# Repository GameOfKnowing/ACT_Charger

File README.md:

# ACT_Charger
A modular, Arduino-based charger for charging and measuring the capacities of many small lithium-polymer batteries

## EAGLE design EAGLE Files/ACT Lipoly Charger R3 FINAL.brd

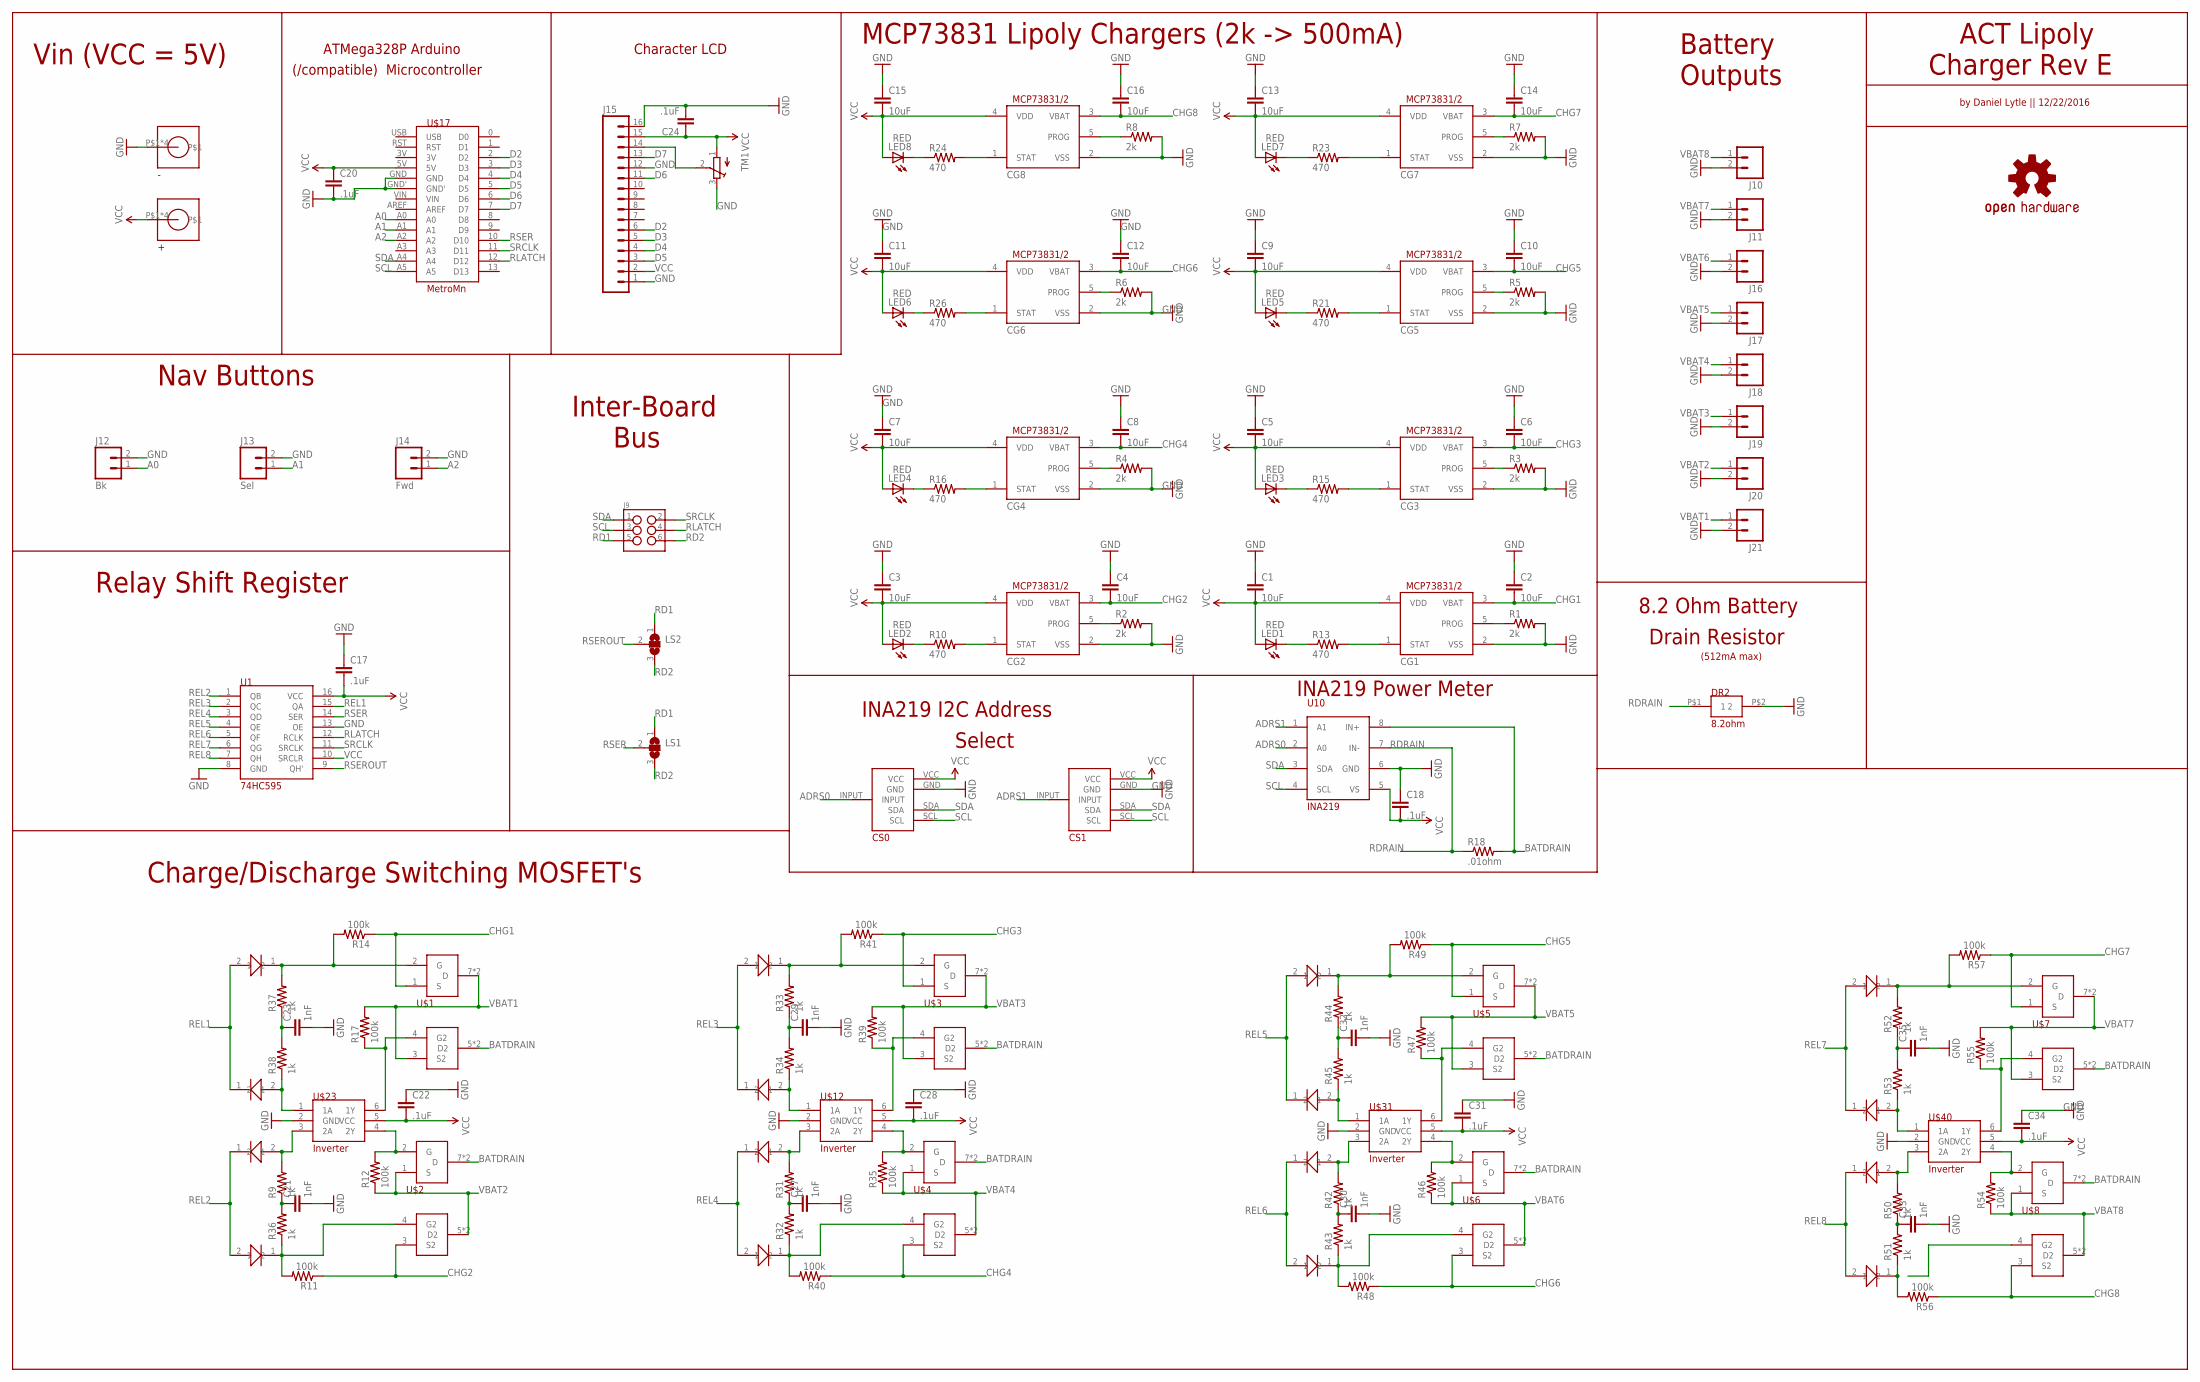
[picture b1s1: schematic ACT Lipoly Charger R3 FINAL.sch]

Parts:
+: 8191-SEMS; 9191-SEMS
-: 8191-SEMS; 9191-SEMS
C1, C2, C3, C4, C5, C6, C7, C8, C9, C10, C11, C12, C13, C14, C15, C16: 10uF; 0805
C17, C18, C20, C22, C24, C28, C31, C34: .1uF; 0805
C21, C23, C27, C29, C30, C32, C33, C35: 1nF; 0805
CG1, CG2, CG3, CG4, CG5, CG6, CG7, CG8: MCP73831/OT; SOT23-5L
CS0, CS1: 4-WAYSELECTOR
DR2: 8.2ohm; UB5C-5R6F1
J9: M03X2FEMALE; 2X3
J10, J11, J16, J17, J18, J19, J20, J21: M02LOCK_LONGPADS; 1X02_LOCK_LONGPADS
J12: Bk; 1X02_LOCK_LONGPADS
J13: Sel; 1X02_LOCK_LONGPADS
J14: Fwd; 1X02_LOCK_LONGPADS
J15: M16LOCK_LONGPADS; 1X16_LOCK_LONGPADS
LED1, LED2, LED3, LED4, LED5, LED6, LED7, LED8: RED; CHIP-LED0805
LS1, LS2: SJ2W; SJ_2
R1, R2, R3, R4, R5, R6, R7, R8: 2k; 0805
R9, R31, R32, R33, R34, R36, R37, R38, R42, R43, R44, R45, R50, R51, R52, R53: 1k; 0805
R10, R13, R15, R16, R21, R23, R24, R26: 470; 0805
R11, R12, R14, R17, R35, R39, R40, R41, R46, R47, R48, R49, R54, R55, R56, R57: 100k; 0805
R18: .01ohm; 0805
TM1: TRIMPOTTC33X; TC33X
U1: 74HC595; DIL16
U10: INA219; SOIC8
U$1, U$2, U$3, U$4, U$5, U$6, U$7, U$8: DMP3085LSD; SOIC8
U$12, U$23, U$31, U$40: Inverter; SOT363_PHILIPS
U$15, U$16, U$18, U$19, U$26, U$27, U$28, U$29, U$34, U$35, U$36, U$37, U$43, U$44, U$45, U$46: DA2J10100L_DIODE; SOD323
U$17: MetroMn; ADAFRUIT_METRO_MINI
VCC: OSHW-LOGOM-COPPER; OSHW-LOGO-M_COPPER

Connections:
A0: J12.1, U$17.A0
A1: J13.1, U$17.A1
A2: J14.1, U$17.A2
ADRS0: CS0.INPUT, U10.2 (A0)
ADRS1: CS1.INPUT, U10.1 (A1)
BATDRAIN: R18.2, U10.8 (IN+), U$1.5 (D2), U$1.6 (D2), U$2.7 (D), U$2.8 (D), U$3.5 (D2), U$3.6 (D2), U$4.7 (D), U$4.8 (D), U$5.5 (D2), U$5.6 (D2), U$6.7 (D), U$6.8 (D), U$7.5 (D2), U$7.6 (D2), U$8.7 (D), U$8.8 (D)
CHG1: C2.2, CG1.3 (VBAT), R14.1, U$1.1 (S)
CHG2: C4.2, CG2.3 (VBAT), R11.1, U$2.3 (S2)
CHG3: C6.2, CG3.3 (VBAT), R41.1, U$3.1 (S)
CHG4: C8.2, CG4.3 (VBAT), R40.1, U$4.3 (S2)
CHG5: C10.2, CG5.3 (VBAT), R49.1, U$5.1 (S)
CHG6: C12.2, CG6.3 (VBAT), R48.1, U$6.3 (S2)
CHG7: C14.2, CG7.3 (VBAT), R57.1, U$7.1 (S)
CHG8: C16.2, CG8.3 (VBAT), R56.1, U$8.3 (S2)
D2: J15.6, U$17.2 (D2)
D3: J15.5, U$17.3 (D3)
D4: J15.4, U$17.4 (D4)
D5: J15.3, U$17.5 (D5)
D6: J15.11, U$17.6 (D6)
D7: J15.13, U$17.7 (D7)
GND: -.P$1, -.P$2, -.P$3, -.P$4, C1.1, C2.1, C3.1, C4.1, C5.1, C6.1, C7.1, C8.1, C9.1, C10.1, C11.1, C12.1, C13.1, C14.1, C15.1, C16.1, C17.1, C18.1, C20.2, C21.2, C22.1, C23.2, C24.2, C27.2, C28.1, C29.2, C30.2, C31.1, C32.2, C33.2, C34.1, C35.2, CG1.2 (VSS), CG2.2 (VSS), CG3.2 (VSS), CG4.2 (VSS), CG5.2 (VSS), CG6.2 (VSS), CG7.2 (VSS), CG8.2 (VSS), CS0.GND, CS1.GND, DR2.P$2 (2), J10.2, J11.2, J12.2, J13.2, J14.2, J15.1, J15.12, J15.16, J16.2, J17.2, J18.2, J19.2, J20.2, J21.2, R1.2, R2.2, R3.2, R4.2, R5.2, R6.2, R7.2, R8.2, TM1.3 (E), U1.8 (GND), U1.13 (OE), U10.6 (GND), U$12.2 (GND), U$17.GND, U$17.GND', U$23.2 (GND), U$31.2 (GND), U$40.2 (GND)
unnamed: CG7.1 (STAT), R23.2
unnamed: CG8.5 (PROG), R8.1
unnamed: LED7.C, R23.1
unnamed: CG7.5 (PROG), R7.1
unnamed: CG6.5 (PROG), R6.1
unnamed: CG8.1 (STAT), R24.2
unnamed: CG5.5 (PROG), R5.1
unnamed: CG4.5 (PROG), R4.1
unnamed: LED8.C, R24.1
unnamed: CG3.5 (PROG), R3.1
unnamed: CG2.5 (PROG), R2.1
unnamed: LED6.C, R26.1
unnamed: CG1.5 (PROG), R1.1
unnamed: CG6.1 (STAT), R26.2
unnamed: CG4.1 (STAT), R16.2
unnamed: LED4.C, R16.1
unnamed: LED5.C, R21.1
unnamed: CG5.1 (STAT), R21.2
unnamed: LED3.C, R15.1
unnamed: CG3.1 (STAT), R15.2
unnamed: LED1.C, R13.1
unnamed: CG1.1 (STAT), R13.2
unnamed: CG2.1 (STAT), R10.2
unnamed: LED2.C, R10.1
unnamed: J15.14, TM1.2 (S)
unnamed: R38.1, U$23.1 (1A), U$29.2
unnamed: R9.2, U$23.3 (2A), U$28.2
unnamed: C21.1, R9.1, R36.2
unnamed: R11.2, R36.1, U$2.4 (G2), U$26.1
unnamed: R12.2, U$2.2 (G), U$23.4 (2Y)
unnamed: R17.1, U$1.4 (G2), U$23.6 (1Y)
unnamed: C23.1, R37.1, R38.2
unnamed: R14.2, R37.2, U$1.2 (G), U$27.1
unnamed: R31.2, U$12.3 (2A), U$16.2
unnamed: C27.1, R31.1, R32.2
unnamed: R32.1, R40.2, U$4.4 (G2), U$15.1
unnamed: R35.2, U$4.2 (G), U$12.4 (2Y)
unnamed: R34.1, U$12.1 (1A), U$19.2
unnamed: R39.1, U$3.4 (G2), U$12.6 (1Y)
unnamed: R33.2, R41.2, U$3.2 (G), U$18.1
unnamed: C29.1, R33.1, R34.2
unnamed: R42.2, U$31.3 (2A), U$35.2
unnamed: C30.1, R42.1, R43.2
unnamed: R43.1, R48.2, U$6.4 (G2), U$34.1
unnamed: R46.2, U$6.2 (G), U$31.4 (2Y)
unnamed: R45.1, U$31.1 (1A), U$37.2
unnamed: R47.1, U$5.4 (G2), U$31.6 (1Y)
unnamed: R44.2, R49.2, U$5.2 (G), U$36.1
unnamed: C32.1, R44.1, R45.2
unnamed: R50.2, U$40.3 (2A), U$44.2
unnamed: C33.1, R50.1, R51.2
unnamed: R51.1, R56.2, U$43.1
unnamed: R54.2, U$8.2 (G), U$40.4 (2Y)
unnamed: R53.1, U$40.1 (1A), U$46.2
unnamed: R55.1, U$7.4 (G2), U$40.6 (1Y)
unnamed: R52.2, R57.2, U$7.2 (G), U$45.1
unnamed: C35.1, R52.1, R53.2
RD1: J9.5, LS1.1, LS2.1
RD2: J9.6, LS1.3, LS2.3
RDRAIN: DR2.P$1 (1), R18.1, U10.7 (IN-)
REL1: U1.15 (QA), U$27.2, U$29.1
REL2: U1.1 (QB), U$26.2, U$28.1
REL3: U1.2 (QC), U$18.2, U$19.1
REL4: U1.3 (QD), U$15.2, U$16.1
REL5: U1.4 (QE), U$36.2, U$37.1
REL6: U1.5 (QF), U$34.2, U$35.1
REL7: U1.6 (QG), U$45.2, U$46.1
REL8: U1.7 (QH), U$43.2, U$44.1
RLATCH: J9.4, U1.12 (RCLK), U$17.12 (D12)
RSER: LS1.2, U1.14 (SER), U$17.10 (D10)
RSEROUT: LS2.2, U1.9 (QH')
SCL: CS0.SCL, CS1.SCL, J9.3, U10.4 (SCL), U$17.A5
SDA: CS0.SDA, CS1.SDA, J9.1, U10.3 (SDA), U$17.A4
SRCLK: J9.2, U1.11 (SRCLK), U$17.11 (D11)
VBAT1: J21.1, R17.2, U$1.3 (S2), U$1.7 (D), U$1.8 (D)
VBAT2: J20.1, R12.1, U$2.1 (S), U$2.5 (D2), U$2.6 (D2)
VBAT3: J19.1, R39.2, U$3.3 (S2), U$3.7 (D), U$3.8 (D)
VBAT4: J18.1, R35.1, U$4.1 (S), U$4.5 (D2), U$4.6 (D2)
VBAT5: J17.1, R47.2, U$5.3 (S2), U$5.7 (D), U$5.8 (D)
VBAT6: J16.1, R46.1, U$6.1 (S), U$6.5 (D2), U$6.6 (D2)
VBAT7: J11.1, R55.2, U$7.3 (S2), U$7.7 (D), U$7.8 (D)
VBAT8: J10.1, R54.1, U$8.1 (S), U$8.5 (D2), U$8.6 (D2)
VCC: +.P$1, +.P$2, +.P$3, +.P$4, C1.2, C3.2, C5.2, C7.2, C9.2, C11.2, C13.2, C15.2, C17.2, C18.2, C20.1, C22.2, C24.1, C28.2, C31.2, C34.2, CG1.4 (VDD), CG2.4 (VDD), CG3.4 (VDD), CG4.4 (VDD), CG5.4 (VDD), CG6.4 (VDD), CG7.4 (VDD), CG8.4 (VDD), CS0.VCC, CS1.VCC, J15.2, J15.15, LED1.A, LED2.A, LED3.A, LED4.A, LED5.A, LED6.A, LED7.A, LED8.A, TM1.1 (A), U1.10 (SRCLR), U1.16 (VCC), U10.5 (VS), U$12.5 (VCC), U$17.5V, U$23.5 (VCC), U$31.5 (VCC), U$40.5 (VCC)

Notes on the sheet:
ATMega328P Arduino
(/compatible) Microcontroller
Vin (VCC = 5V)
Character LCD
MCP73831 Lipoly Chargers (2k -> 500mA)
Relay Shift Register
Inter-Board
Bus
INA219 I2C Address
Select
INA219 Power Meter
8.2 Ohm Battery
Drain Resistor
Battery
Charge/Discharge Switching MOSFET's
ACT Lipoly
Charger Rev E
by Daniel Lytle || 12/22/2016
Outputs
Nav Buttons
(512mA max)

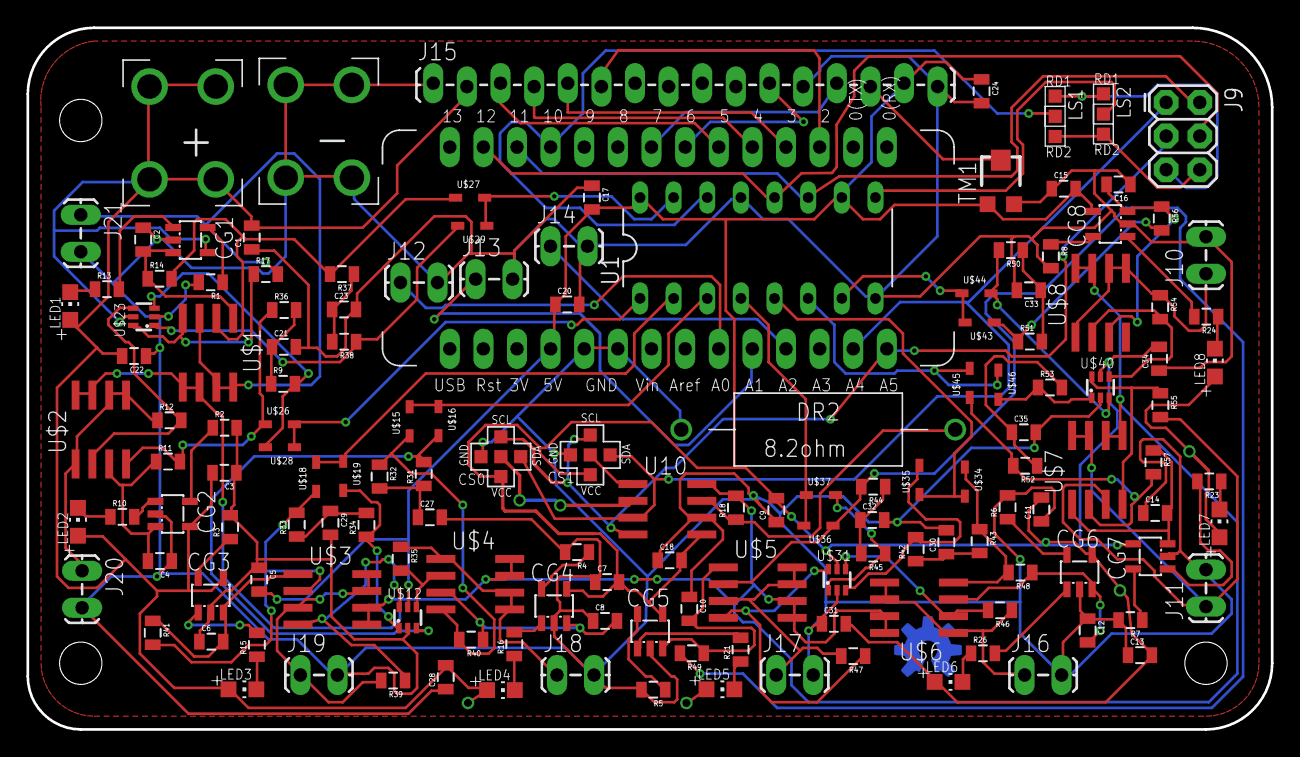
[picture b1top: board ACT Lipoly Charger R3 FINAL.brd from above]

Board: 2 copper layers, 94.0 x 53.0 mm, 150 parts (1 on the bottom side), 104 nets.

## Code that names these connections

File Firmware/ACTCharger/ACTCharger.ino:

//ACT Charger Firmware V. 1.3 
//Manages battery charging, discharging, and UI device functions
//This project's hardware and software are open-source under an MIT License
//GitHub: github.com/codebylytle/ACT_Charger
//by Daniel Lytle
//for the ACT (Automated Coordination of Teams) Lab at USC
//Lab Website: usc-actlab.github.io
//6.13.17
//

#include <Arduino.h>
#include <LiquidCrystal.h>
#include <Wire.h>
#include <Adafruit_INA219.h>

//initializes INA219 modues and their i2c addresses
Adafruit_INA219 ina219_A(0x40);
Adafruit_INA219 ina219_B(0x41);
Adafruit_INA219 ina219_C(0x42);
Adafruit_INA219 ina219_D(0x43);
Adafruit_INA219 ina219_E(0x44);
Adafruit_INA219 ina219_F(0x45);
Adafruit_INA219 ina219_G(0x46);
Adafruit_INA219 ina219_H(0x47);

//sets number of boards in current setup and the number of charging modules per board
const byte numBoards = 2;
const byte chargersperBoard = 8;
//sets minimum voltage (mV) that cells can reach during discharge
const float minV = 3.6;
//sets variable names for shift register pins
const byte RSER = 10;
const byte SRCLK = 11;
const byte RLATCH = 12;
//Names pushbutton pins
const int sel = A1;
const int fw = A2;
const int bk = A0;
//creates an array of bytes, each of which creates a different charge/discharge arrangement when
//shifted into the shift registers
byte registerBytes[9] = {0x00, 0x01, 0x02, 0x04, 0x08, 0x0F, 0x20, 0x40, 0x80};
//a friendlier decimal record of which module on each board is discharging
unsigned short discharging[numBoards];
//tracks the capacity of each battery during and after discharge
float batCap[numBoards][chargersperBoard];
//creates variables used in recording elapsed time between voltage & current readings. Used in battery capacity summations.
unsigned long prevTime;
//creates arrays that store the most recent current and voltage readings from each INA219 sensor
float vBat[numBoards];
float iReading[numBoards];
//tracks whether the system as a whole is in datalogging mode or simply charging all batteries. (0 = charging. 1 = discharging)
char mode = 0;
//tracks whether the system is tethered and using the serial monitor or untethered and using the LCD & pushbutton interface (0 = LCD. 1 = Serial)
char displayMode = 1;

//defines pins used for the LCD
LiquidCrystal lcd(7, 6, 2, 3, 4, 5);


void setup() {
  //initializes sensors
  initSensors();
  
  //Sets shift register pins as outputs
  initRegisters();
  
  //begins charging all batteries
  chargeAll();
  chargeAll();

  
  if(displayMode){
    //initializes the serial console
    initSerial();
  }
  else{
  //Sets UI button pins as inputs & enables corresponding internal pullup resistors
  initButtons();
  //initializes the LCD display (16x2 by default)
  initLCD();
  }
  
  //takes user input to determine whether to charge or discharge batteries
  getmodeInput();
}

void loop() {
  if(mode == 1){
    //reads voltage and current from each INA219, and updates capacity measurements accordingly
    getV();
    getI();
    logPower();

    //displays information on the progress of the discharge
    displayProgress();
    
    //Moves on to the next battery if the one currently discharging has reached the minimum voltage
    checkMinV();

    delay(1000);

    //switches to charging mode if all batteries are done discharging
    mode = 0;
    for(int i = 0; i < numBoards; i++){
      if(discharging[i]){
        mode = 1;
      }
    }
    
    //if the mode has changed to charging mode, charge all batteries and display collected data
    if(!mode){
      chargeAll();
      outputData();
    }
  }
}

//switches to the next battery or ends the charging cycle if
//a discharging battery's voltage falls below minV
void checkMinV(){
  for(int i = 0; i < numBoards; i++){
    if(vBat[i] < minV && discharging[i]){
      discharging[i] ++;
      if(discharging[i] >= chargersperBoard){
        discharging[i] = 0;
      }
      regUpdate();
    }
  }
}

//Initializes shift register control pins as outputs
void initRegisters(){
  pinMode(RSER, OUTPUT);
  pinMode(SRCLK, OUTPUT);
  pinMode(RLATCH, OUTPUT);
}

//intiializes UI button pins as inputs & enables corresponding pullups
void initButtons(){
  pinMode(sel, INPUT_PULLUP);
  pinMode(fw, INPUT_PULLUP);
  pinMode(bk, INPUT_PULLUP);
}

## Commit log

2017-05-19 Initial commit adds board files and firmware
2017-05-19 Adds a more descriptive header comment
2017-06-13 Improves UI and discharge switching efficiency
2017-06-16 Update LICENSE
2017-06-29 Adds .stl files of first enclosure Rev.A
2017-07-01 Add charger manual
2017-07-26 Adds unibody case design, removes modudular case
2017-07-28 Widened case body mounting holes
2017-07-28 Adds holes for USB and display cables
2017-10-17 Adds missing LCD signal traces

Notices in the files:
parts and their libraries:
SparkFun-Capacitors: Licensing: Creative Commons ShareAlike 4.0 International - https://creativecommons.org/licenses/by-sa/4.0
